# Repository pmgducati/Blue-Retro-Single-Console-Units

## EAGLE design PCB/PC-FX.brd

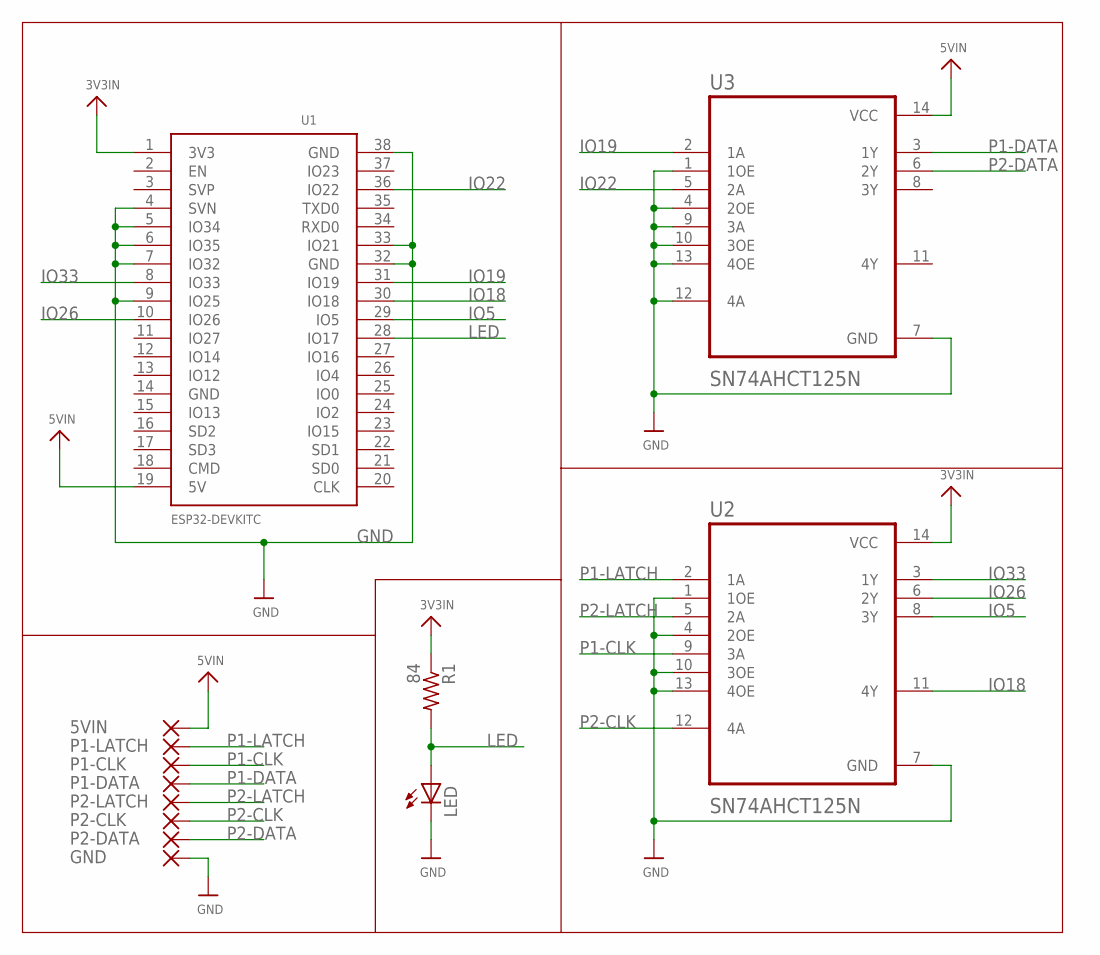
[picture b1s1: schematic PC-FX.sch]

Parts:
5VIN: SMD5; SMD2,54-5,08
GND: SMD5; SMD2,54-5,08
LED: LEDCHIPLED_1206; CHIPLED_1206
P1-CLK, P1-DATA, P1-LATCH, P2-CLK, P2-DATA, P2-LATCH: SMD5; SMD2,54-5,08
R1: 84; R1206
U1: ESP32DEVKITC; ESP32-DEVKITC
U2, U3: SN74AHCT125N; DIP794W45P254L1969H508Q14

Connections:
3V3IN: R1.1, U1.1 (3V3), U2.14 (VCC)
5VIN: 5VIN.1, U1.19 (5V), U3.14 (VCC)
GND: GND.1, LED.C, U1.4 (SVN), U1.5 (IO34), U1.6 (IO35), U1.7 (IO32), U1.9 (IO25), U1.32 (GND), U1.33 (IO21), U1.38 (GND), U2.1 (1OE), U2.4 (2OE), U2.7 (GND), U2.10 (3OE), U2.13 (4OE), U3.1 (1OE), U3.4 (2OE), U3.7 (GND), U3.9 (3A), U3.10 (3OE), U3.12 (4A), U3.13 (4OE)
IO5: U1.29 (IO5), U2.8 (3Y)
IO18: U1.30 (IO18), U2.11 (4Y)
IO19: U1.31 (IO19), U3.2 (1A)
IO22: U1.36 (IO22), U3.5 (2A)
IO26: U1.10 (IO26), U2.6 (2Y)
IO33: U1.8 (IO33), U2.3 (1Y)
LED: LED.A, R1.2, U1.28 (IO17)
P1-CLK: P1-CLK.1, U2.9 (3A)
P1-DATA: P1-DATA.1, U3.3 (1Y)
P1-LATCH: P1-LATCH.1, U2.2 (1A)
P2-CLK: P2-CLK.1, U2.12 (4A)
P2-DATA: P2-DATA.1, U3.6 (2Y)
P2-LATCH: P2-LATCH.1, U2.5 (2A)

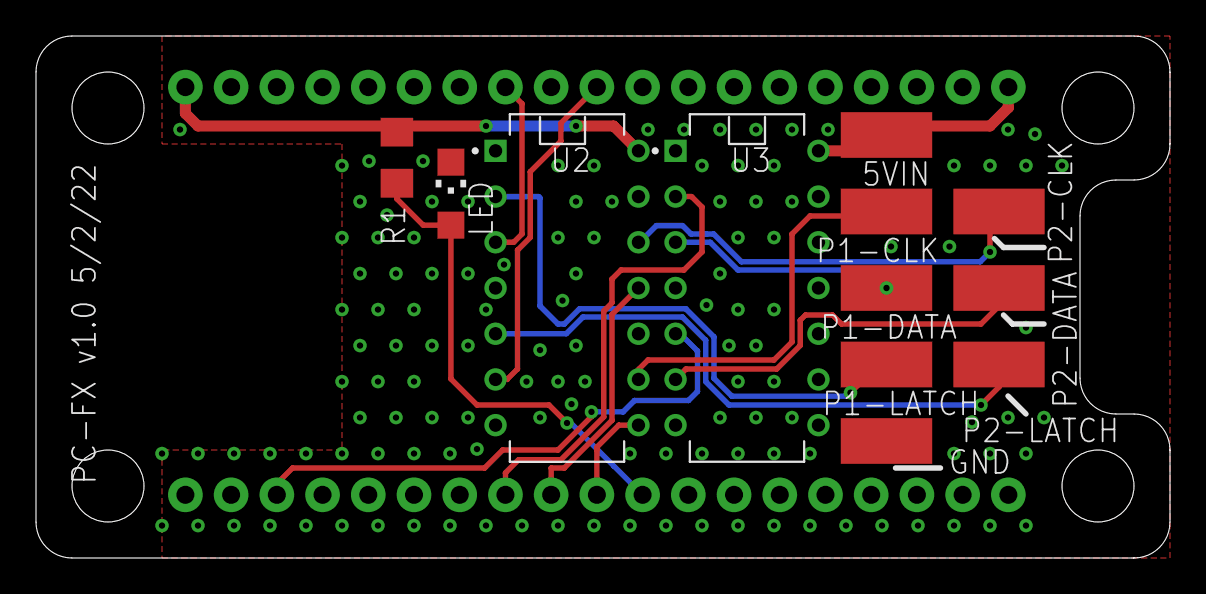
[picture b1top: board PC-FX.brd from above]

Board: 2 copper layers, 63.0 x 29.0 mm, 13 parts (1 on the bottom side), 16 nets.

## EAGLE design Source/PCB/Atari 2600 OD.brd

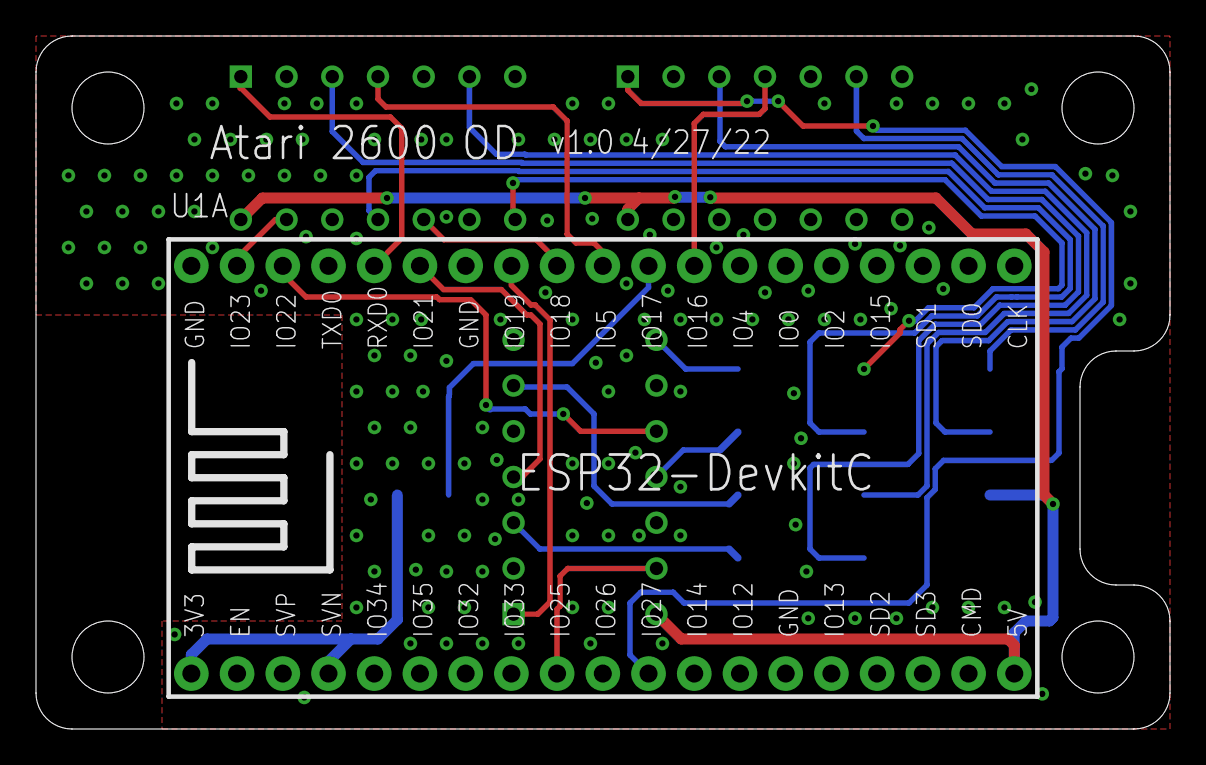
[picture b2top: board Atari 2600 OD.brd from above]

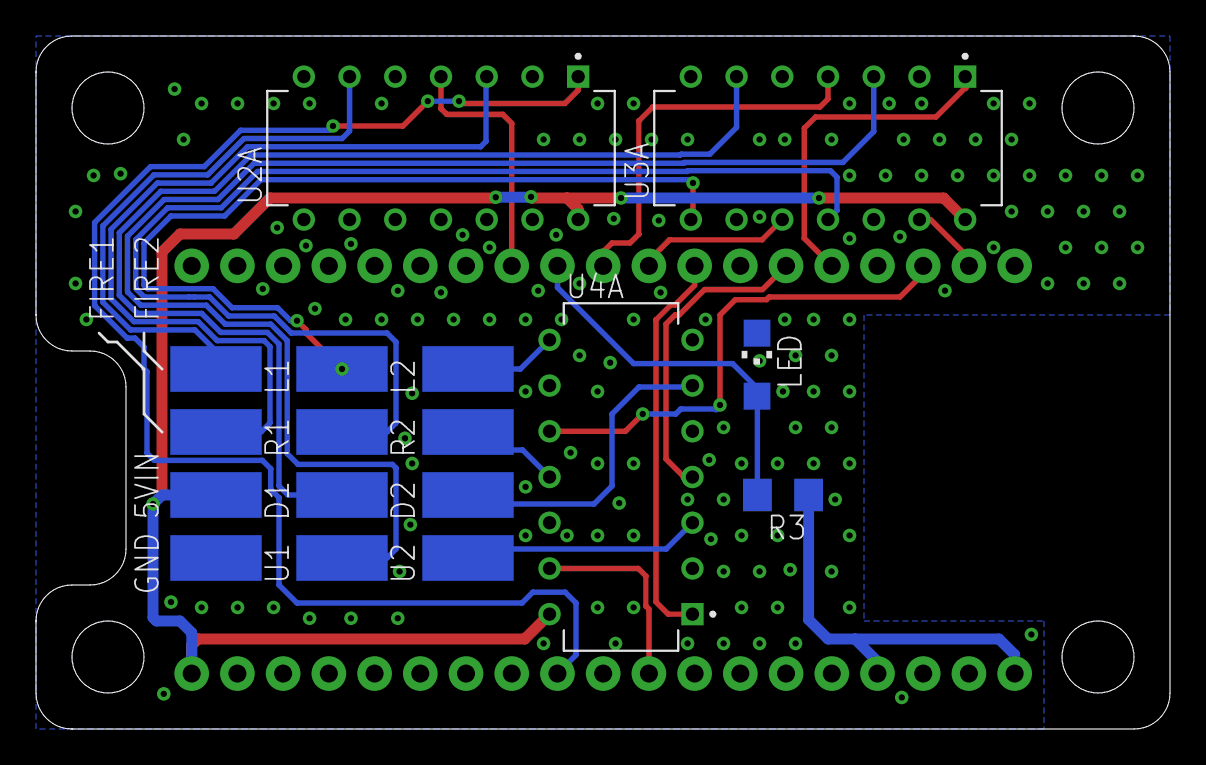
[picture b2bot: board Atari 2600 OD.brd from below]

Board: 2 copper layers, 63.0 x 38.5 mm, 18 parts (17 on the bottom side), 24 nets.

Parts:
5VIN: SMD2,54-5,08
D1, D2: SMD2,54-5,08
FIRE1, FIRE2: SMD2,54-5,08
GND: SMD2,54-5,08
L1, L2: SMD2,54-5,08
LED: CHIPLED_1206
R1, R2: SMD2,54-5,08
R3: 84; R1206
U1, U2: SMD2,54-5,08
U1A: ESP32DEVKITC; ESP32-DEVKITC
U2A, U3A, U4A: SN74AHCT125N; DIP794W45P254L1969H508Q14

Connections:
3V3IN: R3.1, U1A.1, U1A.4
5VIN: 5VIN.1, U1A.19, U2A.14, U3A.14, U4A.14
D1: D1.1, U3A.6
D2: D2.1, U4A.6
FIRE1: FIRE1.1, U2A.3
FIRE2: FIRE2.1, U2A.6
GND: GND.1, LED.C, U1A.5, U1A.6, U1A.7, U1A.38, U2A.2, U2A.5, U2A.7, U2A.9, U2A.10, U2A.12, U2A.13, U3A.2, U3A.5, U3A.7, U3A.9, U3A.12, U4A.2, U4A.5, U4A.7, U4A.9, U4A.12
IO3: U1A.34, U3A.1
IO5: U1A.29, U3A.4
IO16: U1A.27, U2A.4
IO17: LED.A, R3.2, U1A.28
IO18: U1A.30, U3A.10
IO19: U1A.31, U4A.1
IO21: U1A.33, U4A.4
IO22: U1A.36, U4A.10
IO23: U1A.37, U3A.13
IO25: U1A.9, U4A.13
IO27: U1A.11, U2A.1
L1: L1.1, U3A.8
L2: L2.1, U4A.8
R1: R1.1, U3A.11
R2: R2.1, U4A.11
U1: U1.1, U3A.3
U2: U2.1, U4A.3

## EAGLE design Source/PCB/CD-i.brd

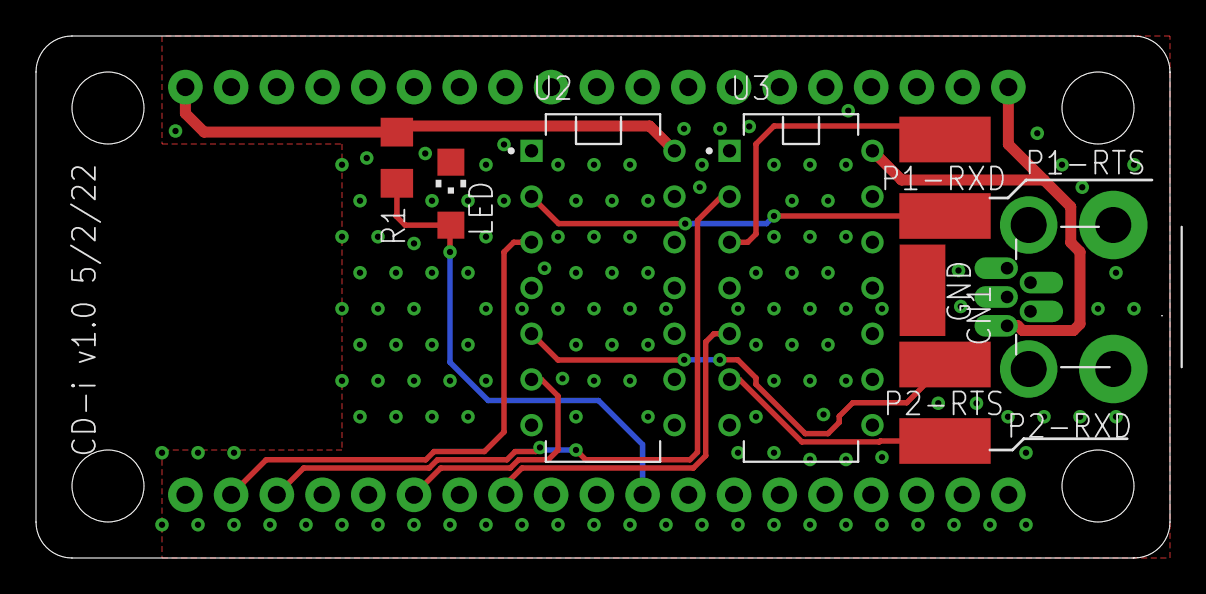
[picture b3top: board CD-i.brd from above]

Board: 2 copper layers, 63.0 x 29.0 mm, 11 parts (1 on the bottom side), 12 nets.

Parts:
CN1: USB-MINIB-THM
GND: SMD2,54-5,08
LED: CHIPLED_1206
P1-RTS, P1-RXD, P2-RTS, P2-RXD: SMD2,54-5,08
R1: 84; R1206
U1: ESP32DEVKITC; ESP32-DEVKITC
U2, U3: SN74AHCT125N; DIP794W45P254L1969H508Q14

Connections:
3V3IN: R1.1, U1.1, U2.14
5VIN: CN1.VBUS, U1.19, U3.14
GND: CN1.GND, GND.1, LED.C, U1.4, U1.5, U1.6, U1.7, U1.8, U1.9, U1.32, U1.38, U2.1, U2.4, U2.7, U2.9, U2.10, U2.12, U2.13, U3.1, U3.4, U3.7, U3.9, U3.10, U3.12, U3.13
IO19: U1.31, U3.5
IO21: U1.33, U2.6
IO22: U1.36, U3.2
IO23: U1.37, U2.3
LED: LED.A, R1.2, U1.28
P1-RTS: P1-RTS.1, U2.2
P1-RXD: P1-RXD.1, U3.3
P2-RTS: P2-RTS.1, U2.5
P2-RXD: P2-RXD.1, U3.6

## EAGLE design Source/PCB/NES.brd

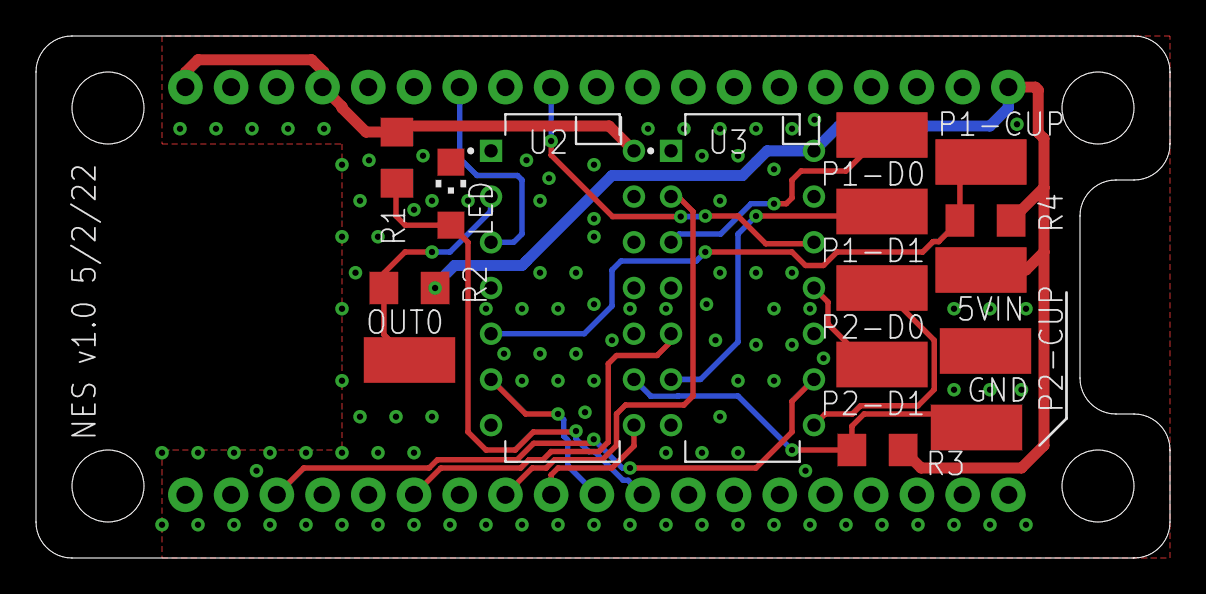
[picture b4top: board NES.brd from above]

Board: 2 copper layers, 63.0 x 29.0 mm, 17 parts (1 on the bottom side), 18 nets.

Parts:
5VIN: SMD2,54-5,08
GND: SMD2,54-5,08
LED: CHIPLED_1206
OUT0: SMD2,54-5,08
P1-CUP, P1-D0, P1-D1, P2-CUP, P2-D0, P2-D1: SMD2,54-5,08
R1: 84; R1206
R2, R3, R4: 3.6K; R1206
U1: ESP32DEVKITC; ESP32-DEVKITC
U2, U3: SN74AHCT125N; DIP794W45P254L1969H508Q14

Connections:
3V3IN: R1.1, U1.1, U1.4, U2.14
5VIN: 5VIN.1, R2.2, R3.2, R4.2, U1.19, U3.14
GND: GND.1, LED.C, U1.5, U1.6, U1.8, U1.32, U1.38, U2.1, U2.4, U2.7, U2.10, U2.12, U2.13, U3.1, U3.4, U3.7, U3.10, U3.13
IO5: U1.29, U2.6
IO18: U1.30, U2.8
IO19: U1.31, U3.2
IO21: U1.33, U3.5
IO22: U1.36, U3.9
IO25: U1.9, U3.12
IO32: U1.7, U2.3
LED: LED.A, R1.2, U1.28
OUT0: OUT0.1, R2.1, U2.2
P1-CUP: P1-CUP.1, R4.1, U2.5
P1-D0: P1-D0.1, U3.3
P1-D1: P1-D1.1, U3.6
P2-CUP: P2-CUP.1, R3.1, U2.9
P2-D0: P2-D0.1, U3.8
P2-D1: P2-D1.1, U3.11

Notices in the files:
parts and their libraries:
microbuilder: This work is placed in the public domain, and may be freely used for commercial and non-commercial work with the following conditions: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
